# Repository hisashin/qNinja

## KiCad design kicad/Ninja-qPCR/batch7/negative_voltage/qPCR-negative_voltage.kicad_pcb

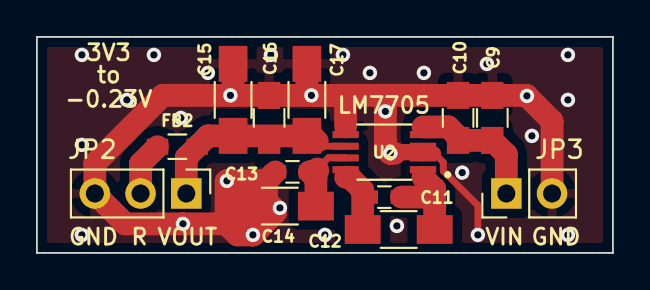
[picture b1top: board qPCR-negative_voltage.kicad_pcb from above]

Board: 2 copper layers, 32.0 x 12.0 mm, 13 parts (0 on the bottom side), 7 nets.

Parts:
C9, C10: 10uF; C_0805_HandSoldering
C11, C13: 4.7uF; C_0603_HandSoldering
C12, C14, C17: DNP; C_1206_HandSoldering
C15: 470nF; C_1206_HandSoldering
C16: 22uF; C_0805_HandSoldering
FB2: 120@100MHz; R_0603_HandSoldering
JP2: Conn_01x03_Male; Pin_Header_Straight_1x03_Pitch2.54mm
JP3: Conn_01x02_Male; Pin_Header_Straight_1x02_Pitch2.54mm
U2: LM7705MMX_NOPB; LM7705MMX-NOPB

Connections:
GND: C9.1, C10.1, C13.1, C14.1, C15.1, C16.1, C17.1, JP2.3, JP3.2, U2.2, U2.3, U2.5
unnamed: C9.2, C10.2, JP3.1, U2.4
unnamed: C11.1, C12.1, U2.8
unnamed: C11.2, C12.2, U2.1
unnamed: C13.2, C14.2, U2.7
unnamed: C15.2, C16.2, C17.2, FB2.2, JP2.1, U2.6
unnamed: FB2.1, JP2.2

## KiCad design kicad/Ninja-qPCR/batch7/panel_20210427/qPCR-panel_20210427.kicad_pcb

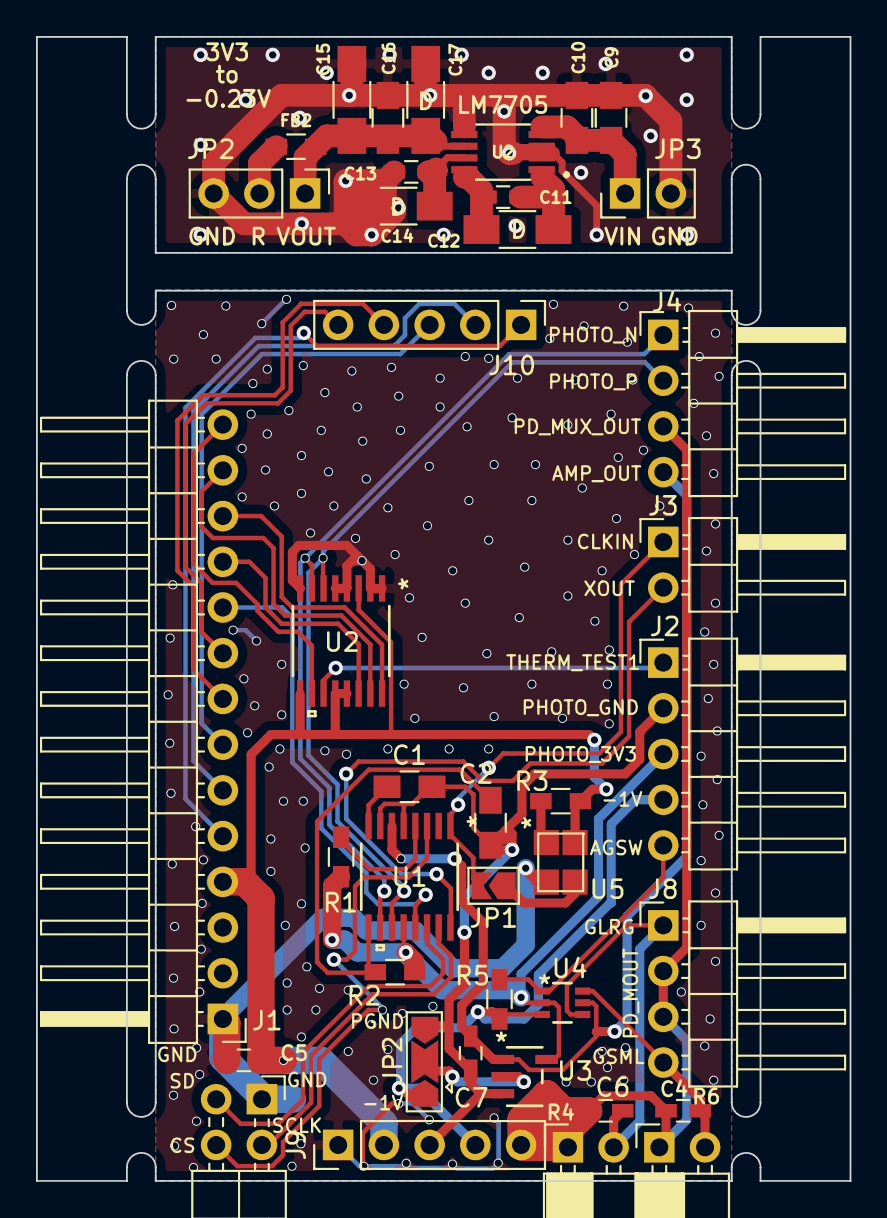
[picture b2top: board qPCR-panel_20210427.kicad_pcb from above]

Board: 2 copper layers, 45.2 x 63.6 mm, 40 parts (0 on the bottom side), 40 nets.

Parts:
C1: 1uF; C_0805_HandSoldering
C2, C9, C10: 10uF; C_0805_HandSoldering
C4, C6: 22pF; C_0603_HandSoldering
C5, C7: 0.1uF; C_0603_HandSoldering
C11, C13: 4.7uF; C_0603_HandSoldering
C12, C14, C17: DNP; C_1206_HandSoldering
C15: 470nF; C_1206_HandSoldering
C16: 22uF; C_0805_HandSoldering
FB2: 120@100MHz; R_0603_HandSoldering
J1: Conn_01x14_Male; Pin_Header_Angled_1x14_Pitch2.54mm
J2: Conn_01x05_Male; Pin_Header_Angled_1x05_Pitch2.54mm
J3: Conn_01x02_Male; Pin_Header_Angled_1x02_Pitch2.54mm
J4, J8: Conn_01x04_Male; Pin_Header_Angled_1x04_Pitch2.54mm
J9, J10: Conn_01x05_Female; Pin_Header_Straight_1x05_Pitch2.54mm
JP1: Jumper; SolderJumper-2_P1.3mm_Open_TrianglePad1.0x1.5mm
JP2: Conn_01x03_Male; Pin_Header_Straight_1x03_Pitch2.54mm
JP2#2: SolderJumper_3_Open; SolderJumper-3_P2.0mm_Open_TrianglePad1.0x1.5mm
JP3: Conn_01x02_Male; Pin_Header_Straight_1x02_Pitch2.54mm
JSPI1: Conn_01x04_Male; Pin_Header_Angled_2x02_Pitch2.54mm
R1, R2, R3, R5: 10K; R_0603_HandSoldering
R4, R6: R; Socket_Strip_Angled_1x02_Pitch2.54mm
U1: ADA2200ARUZ
U2: LM7705MMX_NOPB; LM7705MMX-NOPB
U2#2: ADS1219IPWR
U3: AD8605ARTZ-R2
U4: TS5A9411DCKR
U5: COM1305-0.032768-EXT-T-TR

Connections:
-1V: J2.4, J9.4, JP2#2.1, R5.2, U4.3
/AMP_GAIN_SW: J2.5, R5.1, U4.1
/AMP_OUT: C7.2, J4.4, U1.6, U3.1, U4.5
/GAIN_LARGE: C6.1, J8.1, R4.2, U4.4
/GAIN_SMALL: C4.1, J8.4, R6.2, U4.6
/PHOTO_OUT_N: J4.1, U1.10, U2#2.7
/PHOTO_OUT_P: J4.2, U1.11, U2#2.6
ADC_DRDY: J1.11, U2#2.14
CLKIN: J3.1, JP1.2, U1.1
DEMOD_SPI_CS: JSPI1.4, U1.3
DEMOD_SPI_SCLK: JSPI1.2, U1.15
DEMOD_SPI_SDIO: JSPI1.3, U1.14
GND: C5.2, C9.1, C10.1, C13.1, C14.1, C15.1, C16.1, C17.1, J1.1, J9.1, JP2.3, JP3.2, JSPI1.1, U2.2, U2.3, U2.5, U2#2.1, U2#2.2, U2#2.4, U2#2.5, U2#2.8, U5.2
I2C_SCL: J1.12, U2#2.16
I2C_SDA: J1.13, U2#2.15
unnamed: C1.1, U1.8
unnamed: C2.1, R2.1, U1.9
unnamed: C9.2, C10.2, JP3.1, U2.4
unnamed: C11.1, C12.1, U2.8
unnamed: C11.2, C12.2, U2.1
unnamed: C13.2, C14.2, U2.7
unnamed: C15.2, C16.2, C17.2, FB2.2, JP2.1, U2.6
unnamed: FB2.1, JP2.2
unnamed: JP1.1, U5.3
unnamed: JP2#2.2, U3.2
unnamed: R1.1, U1.4
unnamed: R3.1, U5.1
PD_MUX_GPIO1: J1.9, J10.5
PD_MUX_GPIO2: J1.8, J10.4
PD_MUX_GPIO3: J1.7, J10.3
PD_MUX_GPIO4: J1.6, J10.2
PD_MUX_GPIO5: J1.5, J10.1
PD_MUX_OUT: C4.2, C6.2, J4.3, J8.2, J8.3, J9.5, R4.1, R6.1, U3.4
PD_REF_PWM: J1.10, U1.13
PHOTO_3V3: J2.3, R1.2, R2.2, U1.12, U3.5, U4.2
PHOTO_GND: C1.2, C2.2, C7.1, J2.2, J9.3, JP2#2.3, U1.5, U1.7, U3.3
THERM_TEST1: J2.1, U2#2.11
THERM_WELL: J1.14, U2#2.10
VCC_LOGIC: C5.1, J1.4, J9.2, R3.2, U2#2.3, U2#2.9, U2#2.12, U2#2.13, U5.4
XOUT: J3.2, U1.16

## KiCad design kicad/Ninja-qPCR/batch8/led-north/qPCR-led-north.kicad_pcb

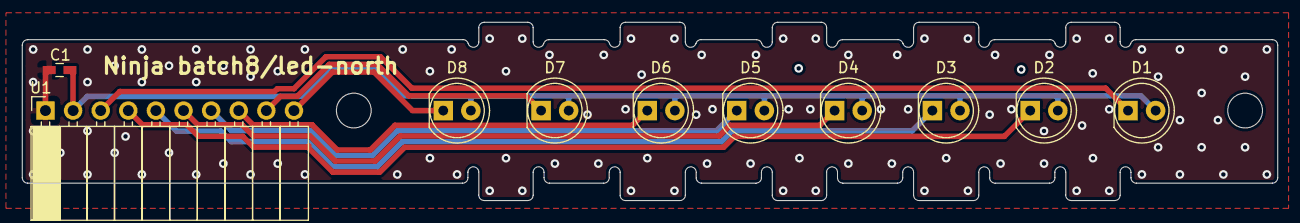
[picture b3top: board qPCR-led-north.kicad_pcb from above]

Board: 2 copper layers, 115.5 x 16.4 mm, 10 parts (0 on the bottom side), 10 nets.

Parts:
C1: C; C_0603_HandSoldering
D1, D2, D3, D4, D5, D6, D7, D8: LED; LED_D5.0mm
U1: Conn_02x05; Socket_Strip_Angled_1x10_Pitch2.54mm

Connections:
GND: C1.2, U1.1
OUT1: D1.1, U1.3
OUT2: D2.1, U1.4
OUT3: D3.1, U1.5
OUT4: D4.1, U1.6
OUT5: D5.1, U1.7
OUT6: D6.1, U1.8
OUT7: D7.1, U1.9
OUT8: D8.1, U1.10
VCC: C1.1, D1.2, D2.2, D3.2, D4.2, D5.2, D6.2, D7.2, D8.2, U1.2

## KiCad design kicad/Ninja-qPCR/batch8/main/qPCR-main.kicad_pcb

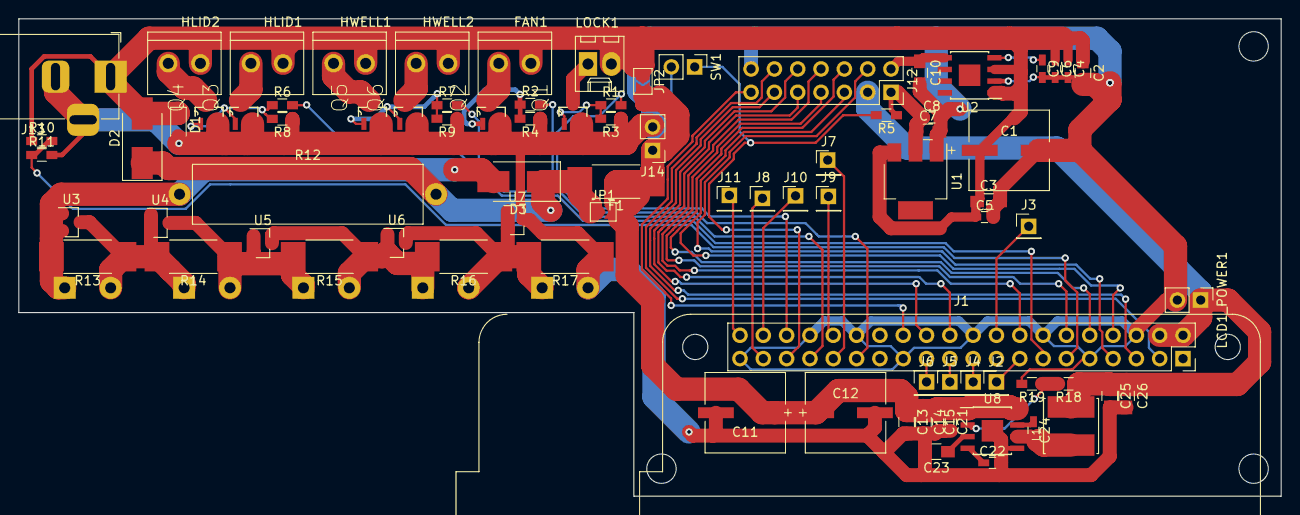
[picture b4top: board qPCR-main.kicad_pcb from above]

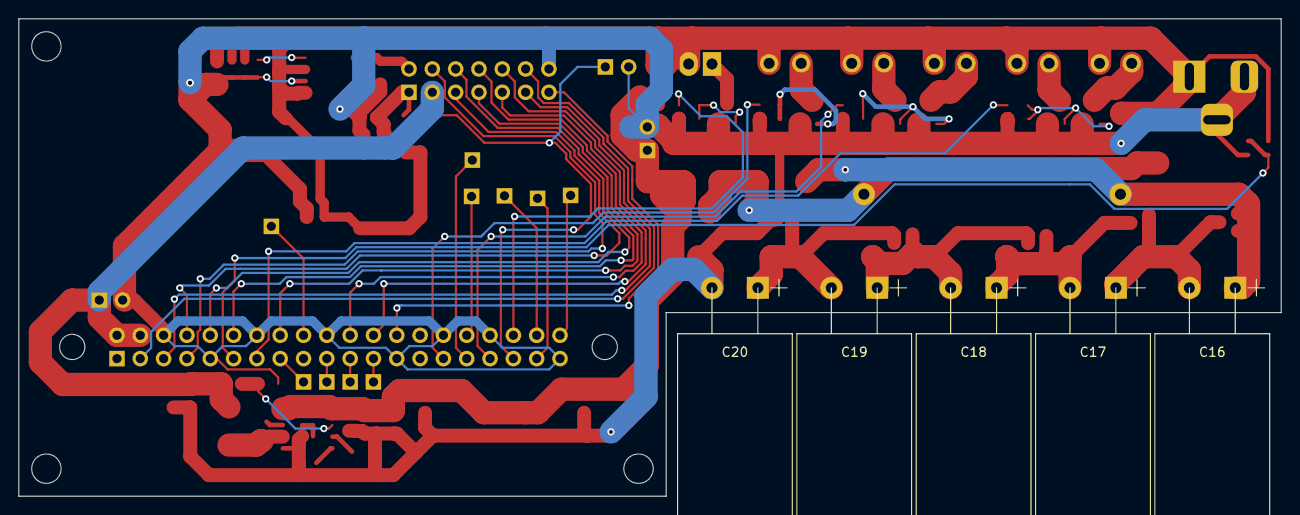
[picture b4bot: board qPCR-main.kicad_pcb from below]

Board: 2 copper layers, 137.5 x 52.0 mm, 88 parts (5 on the bottom side), 55 nets.

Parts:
C1, C11, C12: 100uF; UWX1E101MCL1GB
C2, C10, C13, C14, C23: 4.7uF; C_0805_HandSoldering
C3, C7, C25, C26: 22uF; C_0805_HandSoldering
C4, C5, C8, C15, C24: 0.1uF; C_0603_HandSoldering
C6, C21, C22: 0.01uF; C_0603_HandSoldering
C9: 100pF; C_0603_HandSoldering
C16, C17, C18, C19, C20: 10F2.7V; CP_Radial_D12.5mm_P5.00mm_L34mm
D1: D_Schottky; D_SOD-323_HandSoldering
D2, D3: D; D_SMB_Handsoldering
F1: Fuse; R_2512_HandSoldering
FAN1: Screw_Terminal_01x02; TB_SeeedOPL_320110028
HLID1, HLID2: Screw_Terminal_01x02; TB_SeeedOPL_320110028
HWELL1, HWELL2: Screw_Terminal_01x02; TB_SeeedOPL_320110028
J1: Raspberry_Pi_3A_Plus_wpi; Raspberry_Pi_3A+_3B+_4B_Zero_FaceDown
J2, J3, J4, J5, J6, J7, J8, J9, J10, J11: Conn_01x01_Male; Pin_Header_Straight_1x01_Pitch2.54mm
J12: Conn_01x14_Male; Socket_Strip_Straight_2x07_Pitch2.54mm
J13: Barrel_Jack_Switch; BarrelJack_Horizontal
J14: Conn_01x02_Male; Pin_Header_Straight_1x02_Pitch2.54mm
JP1, JP2: Jumper; SolderJumper-2_P1.3mm_Open_TrianglePad1.0x1.5mm
L1: 3.3uH(ALPS GLMC / TDK SPM6530); SRN6045TA-3R3Y
LCD1_POWER1: Conn_01x02_Male; Pin_Header_Straight_1x02_Pitch2.54mm
LOCK1: Conn_01x02_Male; Molex_KK-6410-02_02x2.54mm_Straight
Q1, Q2, Q3, Q4, Q5, Q6: Q_NMOS_GSD; SOT95P240X112-3N
R1, R2, R6, R7: 150; R_0603_HandSoldering
R3, R4, R5, R8, R9, R10, R19: 47k; R_0603_HandSoldering
R11: 10k; R_0603_HandSoldering
R12: 8.2Ω 3W; R_Axial_Power_L25.0mm_W6.4mm_P27.94mm
R13, R14, R15, R16, R17: 1k2W; R_2512_HandSoldering
R18: 261k; R_0603_HandSoldering
SW1: SW_Reed; Pin_Header_Straight_1x02_Pitch2.54mm
U1: CJT1117-3.3; SOT-223
U2: AP2210K-3.3TRG1; SOIC-8-1EP_3.9x4.9mm_Pitch1.27mm
U3, U4, U5, U6, U7: TL431DBZ; SOT-23
U8: BD9D320EFJ-E2; SOIC-8-1EP_3.9x4.9mm_Pitch1.27mm

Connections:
3V3A: C10.1, J12.2, U2.5
3V3D: C7.1, C8.1, J12.1, R5.1, U1.2
5V_UPS: C25.1, C26.1, J1.2, J1.4, J12.3, L1.2, LCD1_POWER1.1, R18.1
12V: C1.1, C2.1, C3.1, C4.1, C5.1, C6.1, D1.1, D2.2, FAN1.1, HLID1.1, HLID2.1, HWELL1.1, HWELL2.1, J13.1, JP2.1, LOCK1.2, R10.1, U1.3, U2.1, U2.3
12V_BD_VIN: C11.1, C12.1, C13.1, C14.1, C15.1, C21.1, F1.1, J14.1, JP1.2, JP2.2, U8.1, U8.8
/3V3_RASP: J1.1, J1.17
/FAN: J1.29, R2.2
/GPIO3: J1.15, J2.1
/GPIO5: J1.18, J3.1
/GPIO12: J1.19, J4.1
/GPIO13: J1.21, J5.1
/GPIO14: J1.23, J6.1
/GPIO22: J1.31, J7.1
/GPIO25: J1.37, J8.1
/GPIO26: J1.32, J9.1
/GPIO28: J1.38, J10.1
/GPIO29: J1.40, J11.1
/LID_HEATER: J1.13, R6.2
/SheetSupercap/BD_BOOT: C24.1, U8.7
/SheetSupercap/BD_FB: R18.2, R19.1, U8.2
/SheetSupercap/BD_SW: C24.2, L1.1, U8.6
/WELL_HEATER: J1.33, R7.2
ADC_DRDY: J1.24, J12.10
AMP_GAIN_SW: J1.7, J12.4
DLOCK: J1.36, R1.2
DOPEN: J1.35, R5.2, SW1.1
GND: C1.2, C2.2, C3.2, C4.2, C5.2, C6.2, C7.2, C8.2, C9.2, C10.2, C11.2, C12.2, C13.2, C14.2, C15.2, C20.2, C21.2, C22.2, C23.2, C25.2, C26.2, D1.2, J1.6, J1.9, J1.14, J1.20, J1.25, J1.30, J1.34, J1.39, J12.14, J13.2, J13.3, J14.2, LCD1_POWER1.2, Q1.2, Q2.2, Q3.2, Q4.2, Q5.2, Q6.2, R3.1, R4.1, R8.1, R9.1, R11.2, R17.1, R19.2, SW1.2, U1.1, U2.2, U7.3, U8.5, U8.9
I2C_SCL: J1.5, J12.11
I2C_SDA: J1.3, J12.12
MUX_S0: J1.16, J12.8
MUX_S1: J1.12, J12.7
MUX_S2: J1.10, J12.6
MUX_S3: J1.8, J12.5
MUX_SELECT: J1.22, J12.9
unnamed: C9.1, U2.4
unnamed: C16.1, D3.2, R12.1, R13.2, U3.1, U3.2
unnamed: C16.2, C17.1, R13.1, R14.2, U3.3, U4.1, U4.2
unnamed: C17.2, C18.1, R14.1, R15.2, U4.3, U5.1, U5.2
unnamed: C18.2, C19.1, R15.1, R16.2, U5.3, U6.1, U6.2
unnamed: C19.2, C20.1, R16.1, R17.2, U6.3, U7.1, U7.2
unnamed: C22.1, U8.4
unnamed: C23.1, U8.3
unnamed: D2.1, D3.1, F1.2, JP1.1, R12.2
unnamed: FAN1.2, Q2.3
unnamed: HLID1.2, Q3.3
unnamed: HLID2.2, Q4.3
unnamed: HWELL1.2, Q5.3
unnamed: HWELL2.2, Q6.3
unnamed: LOCK1.1, Q1.3
unnamed: Q1.1, R1.1, R3.2
unnamed: Q2.1, R2.1, R4.2
unnamed: Q3.1, Q4.1, R6.1, R8.2
unnamed: Q5.1, Q6.1, R7.1, R9.2
THERM_R_SWITCH: J1.26, J12.13
VIN_SENSE: J1.11, R10.2, R11.1

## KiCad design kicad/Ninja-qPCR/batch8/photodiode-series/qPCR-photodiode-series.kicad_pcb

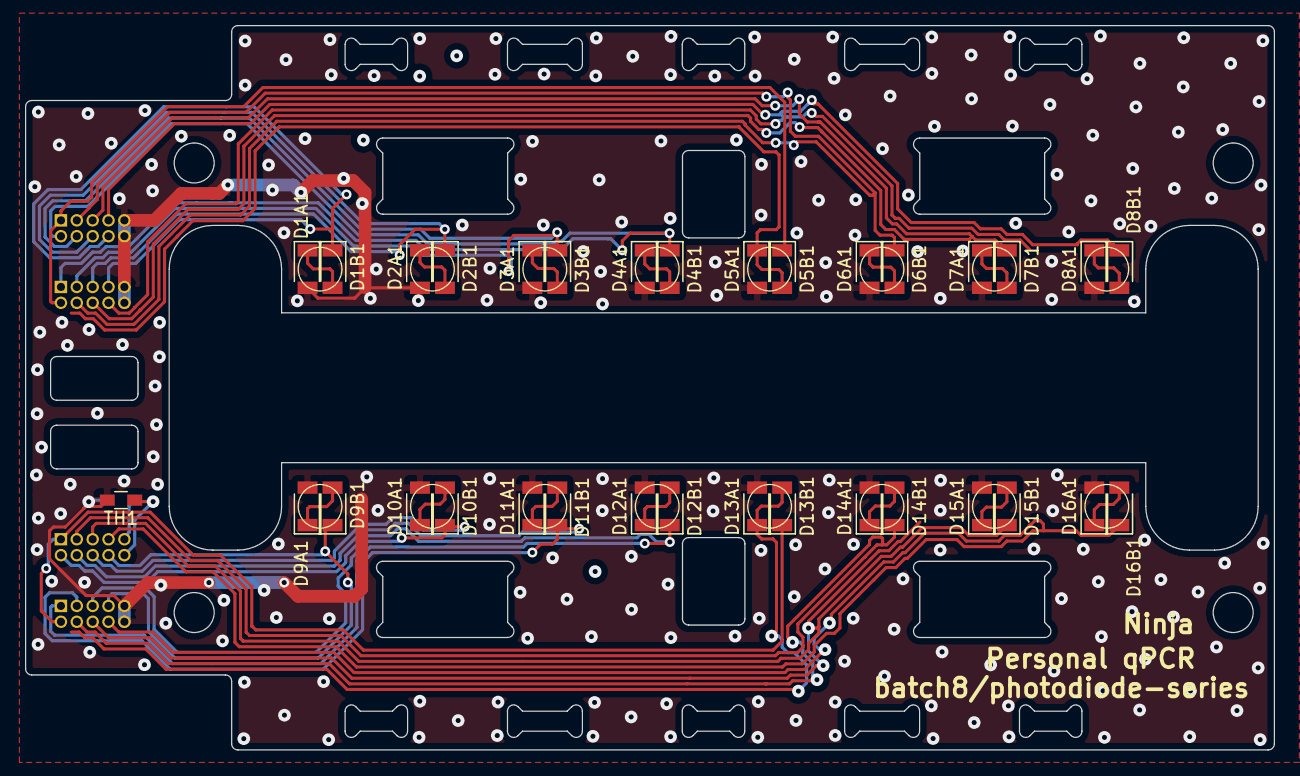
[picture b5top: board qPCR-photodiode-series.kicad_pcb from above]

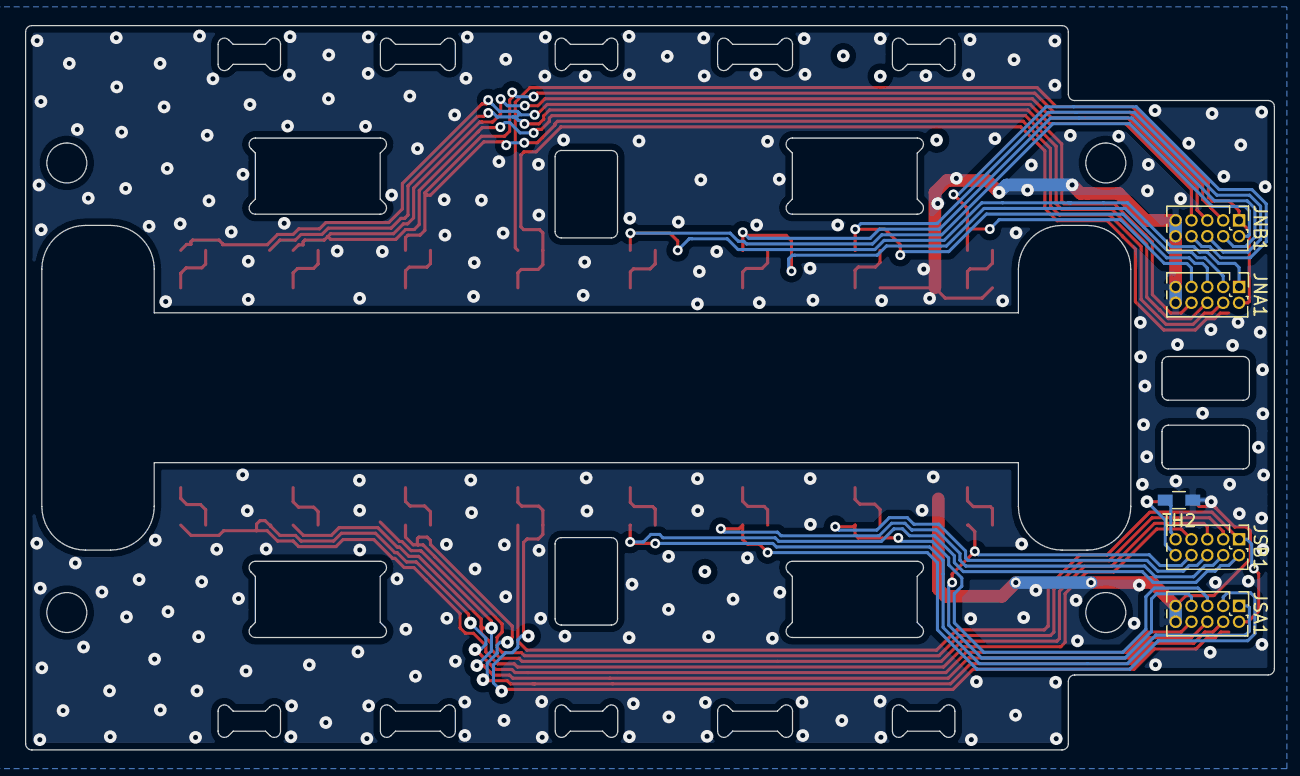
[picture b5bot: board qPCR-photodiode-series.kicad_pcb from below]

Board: 2 copper layers, 100.0 x 58.0 mm, 38 parts (5 on the bottom side), 35 nets.

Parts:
D1A1, D1B1, D2A1, D2B1, D3A1, D3B1, D4A1, D4B1, D5A1, D5B1, D6A1, D6B1, D7A1, D7B1, D8A1, D8B1, D9A1, D9B1, D10A1, D10B1, D11A1, D11B1, D12A1, D12B1, D13A1, D13B1, D14A1, D14B1, D15A1, D15B1, D16A1, D16B1: D_Photo; D_1206
JNA1: Conn_01x10_Male; Pin_Header_Straight_2x05_Pitch1.27mm
JNB1: Conn_01x10_Male; Pin_Header_Straight_2x05_Pitch1.27mm
JSA1: Conn_01x10_Male; Pin_Header_Straight_2x05_Pitch1.27mm
JSB1: Conn_01x10_Male; Pin_Header_Straight_2x05_Pitch1.27mm
TH1, TH2: Thermistor; R_0603_HandSoldering

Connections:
/N_PD_OUT1: D1B1.1, JNA1.7, JNB1.8
/N_PD_OUT3: D2B1.1, JNA1.5, JNB1.6
/N_PD_OUT5: D3B1.1, JNA1.3, JNB1.4
/N_PD_OUT7: D4B1.1, JNA1.1, JNB1.2
/N_PD_OUT9: D5B1.1, JNA1.2, JNB1.1
/N_PD_OUT11: D6B1.1, JNA1.4, JNB1.3
/N_PD_OUT13: D7B1.1, JNA1.6, JNB1.5
/N_PD_OUT15: D8B1.1, JNA1.8, JNB1.7
/S_PD_OUT1: D9B1.1, JSA1.7, JSB1.8
/S_PD_OUT3: D10B1.1, JSA1.5, JSB1.6
/S_PD_OUT5: D11B1.1, JSA1.3, JSB1.4
/S_PD_OUT7: D12B1.1, JSA1.1, JSB1.2
/S_PD_OUT9: D13B1.1, JSA1.2, JSB1.1
/S_PD_OUT11: D14B1.1, JSA1.4, JSB1.3
/S_PD_OUT13: D15B1.1, JSA1.6, JSB1.5
/S_PD_OUT15: D16B1.1, JSA1.8, JSB1.7
GNDA: D1A1.2, D2A1.2, D3A1.2, D4A1.2, D5A1.2, D6A1.2, D7A1.2, D8A1.2, D9A1.2, D10A1.2, D11A1.2, D12A1.2, D13A1.2, D14A1.2, D15A1.2, D16A1.2, JNA1.9, JNA1.10, JNB1.9, JNB1.10, JSA1.9, JSA1.10, TH1.2, TH2.2
unnamed: D1A1.1, D1B1.2
unnamed: D2A1.1, D2B1.2
unnamed: D3A1.1, D3B1.2
unnamed: D4A1.1, D4B1.2
unnamed: D5A1.1, D5B1.2
unnamed: D6A1.1, D6B1.2
unnamed: D7A1.1, D7B1.2
unnamed: D8A1.1, D8B1.2
unnamed: D9A1.1, D9B1.2
unnamed: D10A1.1, D10B1.2
unnamed: D11A1.1, D11B1.2
unnamed: D12A1.1, D12B1.2
unnamed: D13A1.1, D13B1.2
unnamed: D14A1.1, D14B1.2
unnamed: D15A1.1, D15B1.2
unnamed: D16A1.1, D16B1.2
unnamed: JSB1.9, TH2.1
unnamed: JSB1.10, TH1.1

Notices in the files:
parts and their libraries:
Copyright 2016 Accelerated Designs. All rights reserved.
Copyright 2021 Accelerated Designs. All rights reserved.
